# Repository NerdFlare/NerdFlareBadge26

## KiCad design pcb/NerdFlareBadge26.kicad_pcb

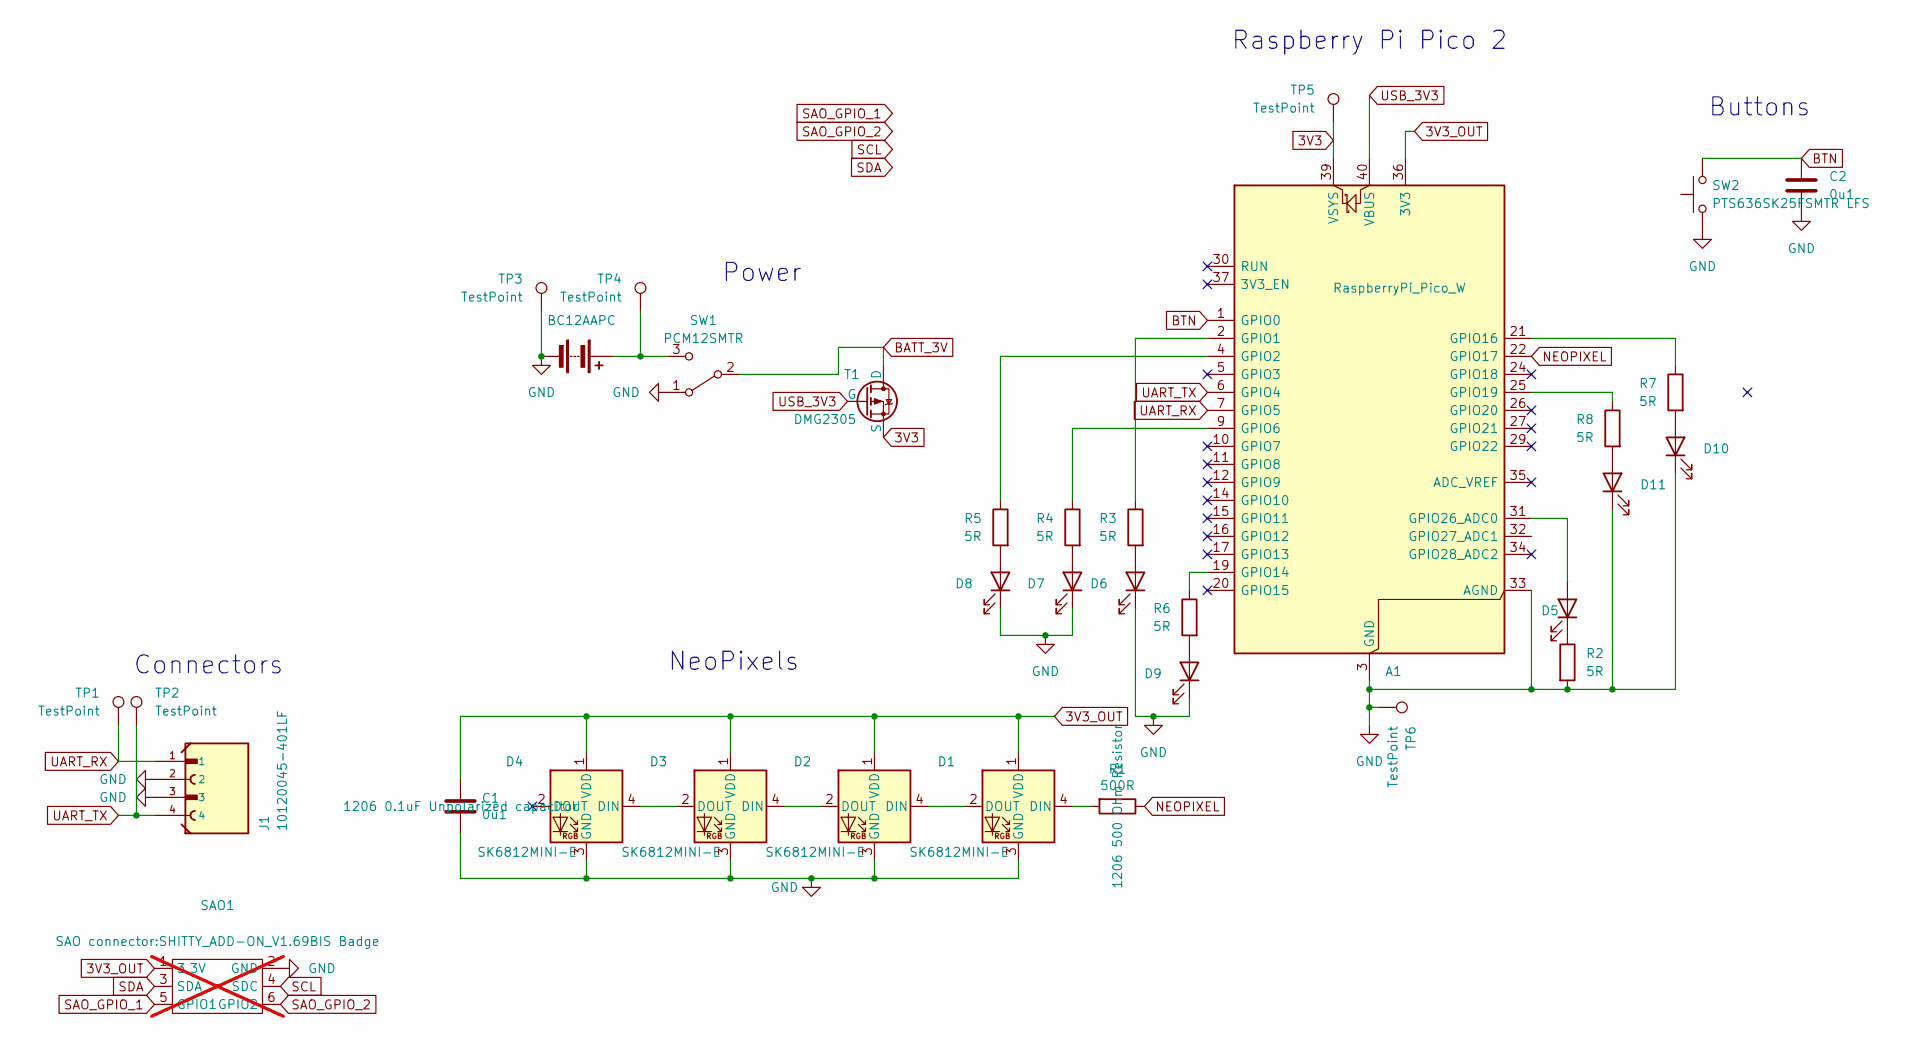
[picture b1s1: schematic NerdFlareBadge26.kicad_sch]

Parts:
A1: RaspberryPi_Pico_W; RPi_Pico_SMD
BT1: BC12AAPC; BAT_BC12AAPC
C1, C2: 0u1; C_1206_3216Metric_Pad1.33x1.80mm_HandSolder
D1, D2, D3, D4: SK6812MINI-E
D5, D6, D7, D8, D9, D10, D11: B1501TW--20P001013U1930; LED_1206_3216Metric_Pad1.42x1.75mm_HandSolder
J1: 10120045-401LF; AMPHENOL_10120045-401LF; PARTREV A
R1: 500R; R_1206_3216Metric_Pad1.30x1.75mm_HandSolder
R2, R3, R4, R5, R6, R7, R8: 5R; R_1206_3216Metric_Pad1.30x1.75mm_HandSolder
SAO1: SHITTY_ADD-ON_V1.69BIS Badge; not fitted
SW1: PCM12SMTR; SW_SPDT_PCM12
SW2: PTS636SK25FSMTR LFS; SMT Tactile Switch CK PTS636SK25FSMTR
T1: DMG2305; SOT-23
TP1, TP2, TP3, TP4, TP5, TP6: TestPoint; TestPoint_Pad_1.5x1.5mm

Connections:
3V3: A1.39 (VSYS), T1.2 (S), TP5.1
3V3_OUT: A1.36 (3V3), C1.1, D1.1 (VDD), D2.1 (VDD), D3.1 (VDD), D4.1 (VDD), SAO1.1 (3.3V)
BATT_3V: SW1.2 (B), T1.3 (D)
BTN: A1.1 (GPIO0), C2.1, SW2.2
GND: A1.3 (GND), A1.8 (GND), A1.13 (GND), A1.18 (GND), A1.23 (GND), A1.28 (GND), A1.33 (AGND), A1.38 (GND), BT1.2 (-), C1.2, C2.2, D1.3 (GND), D2.3 (GND), D3.3 (GND), D4.3 (GND), D6.1 (K), D7.1 (K), D8.1 (K), D9.1 (K), D10.1 (K), D11.1 (K), J1.2, J1.3, R2.2, SAO1.2 (GND), SW1.1 (A), SW2.1, TP3.1, TP6.1
NEOPIXEL: A1.22 (GPIO17), R1.1
unnamed: A1.2 (GPIO1), R3.1
unnamed: A1.4 (GPIO2), R5.1
unnamed: A1.9 (GPIO6), R4.1
unnamed: A1.19 (GPIO14), R6.1
unnamed: A1.21 (GPIO16), R7.1
unnamed: A1.25 (GPIO19), R8.1
unnamed: A1.31 (GPIO26_ADC0), D5.2 (A)
unnamed: BT1.1 (+), SW1.3 (C), TP4.1
unnamed: D1.4 (DIN), R1.2
unnamed: D1.2 (DOUT), D2.4 (DIN)
unnamed: D2.2 (DOUT), D3.4 (DIN)
unnamed: D3.2 (DOUT), D4.4 (DIN)
unnamed: D5.1 (K), R2.1
unnamed: D6.2 (A), R3.2
unnamed: D7.2 (A), R4.2
unnamed: D8.2 (A), R5.2
unnamed: D9.2 (A), R6.2
unnamed: D10.2 (A), R7.2
unnamed: D11.2 (A), R8.2
SAO_GPIO_1: SAO1.5 (GPIO1)
SAO_GPIO_2: SAO1.6 (GPIO2)
SCL: SAO1.4 (SDC)
SDA: SAO1.3 (SDA)
UART_RX: A1.7 (GPIO5), J1.1, TP1.1
UART_TX: A1.6 (GPIO4), J1.4, TP2.1
USB_3V3: A1.40 (VBUS), T1.1 (G)

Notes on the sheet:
Buttons
Power
NeoPixels
Connectors
Raspberry Pi Pico 2

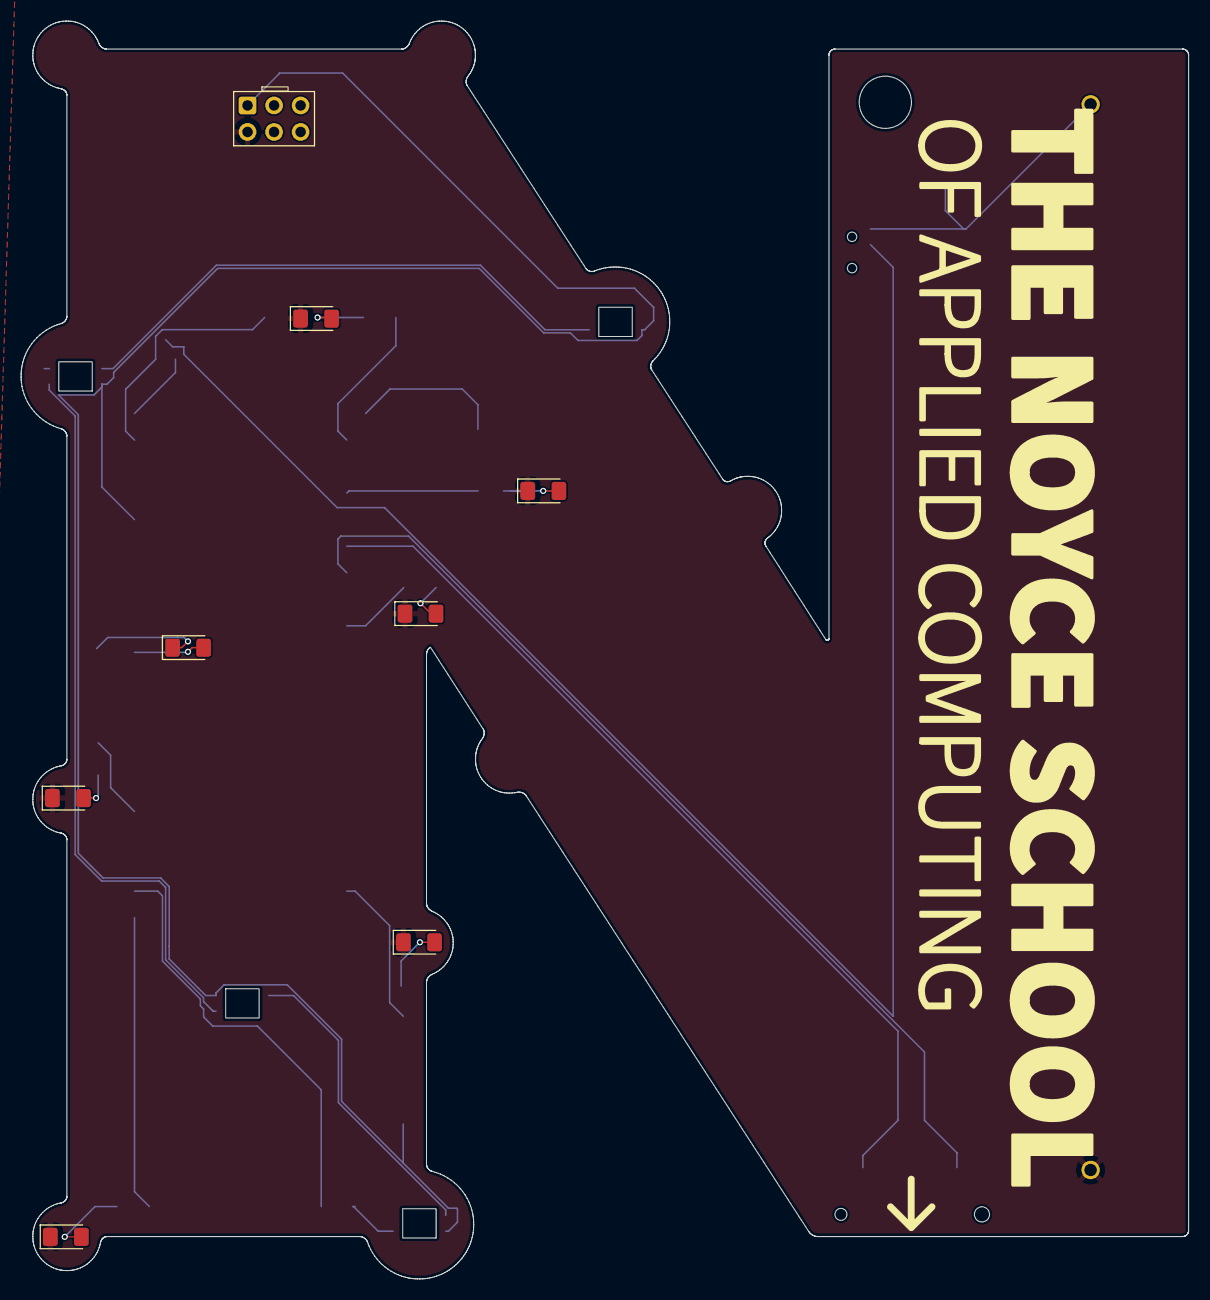
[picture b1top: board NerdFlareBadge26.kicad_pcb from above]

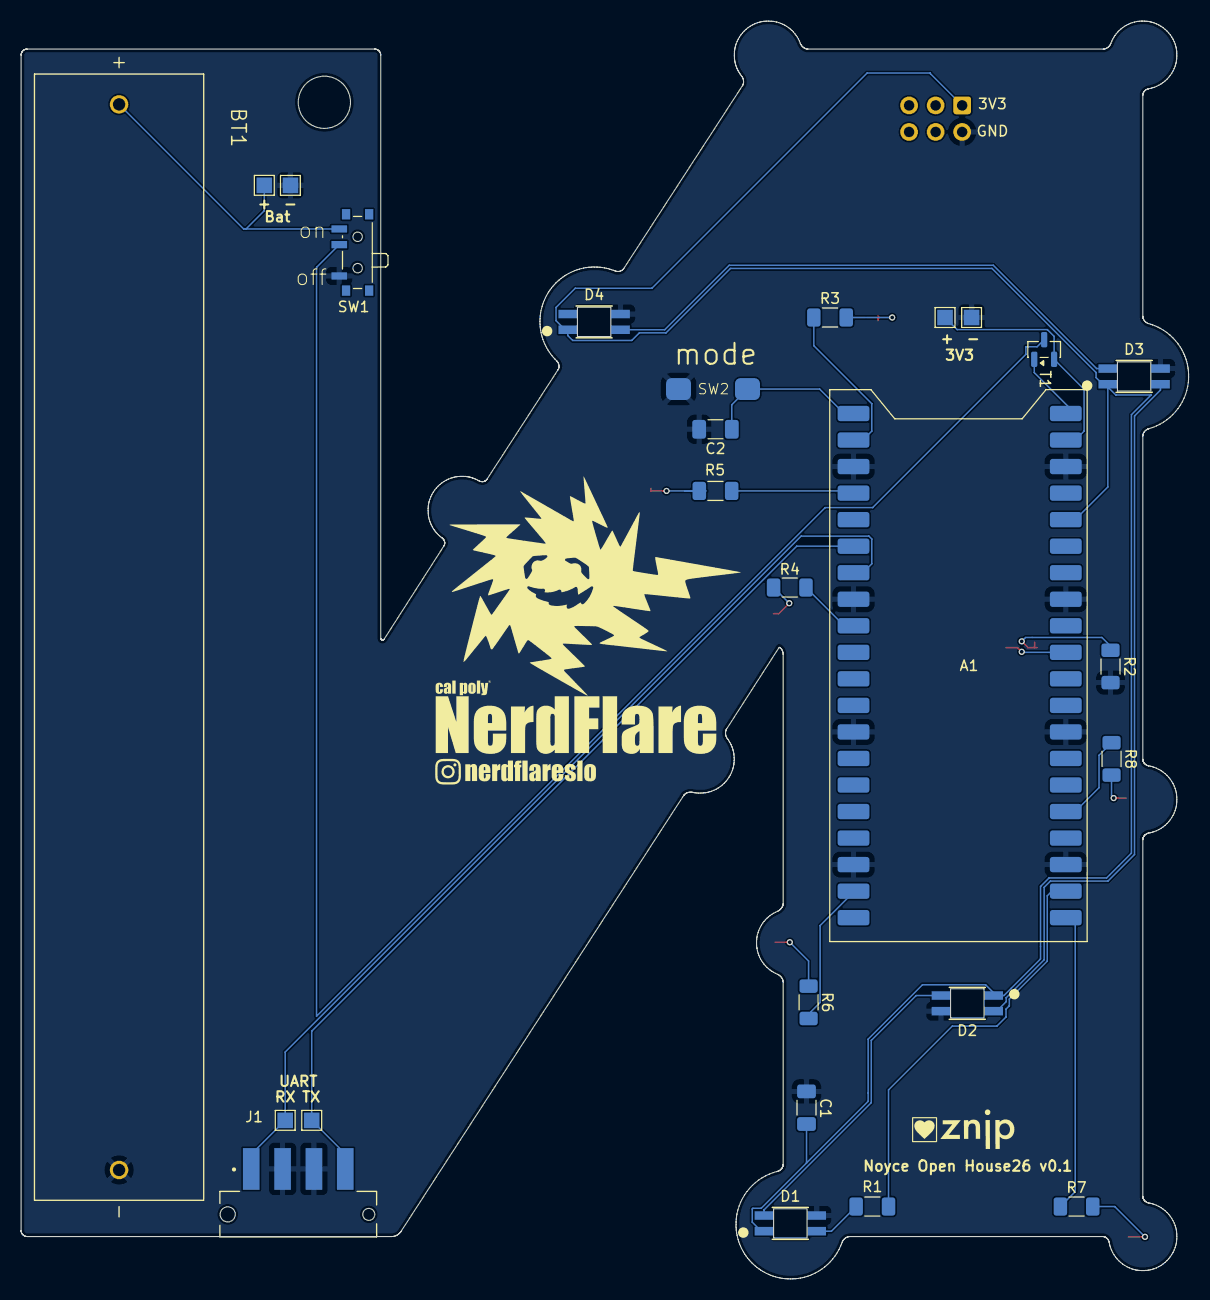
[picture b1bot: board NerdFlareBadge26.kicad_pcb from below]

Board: 2 copper layers, 111.7 x 120.4 mm, 34 parts (22 on the bottom side), 28 nets.

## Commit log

2026-03-31 Initial commit of v0.1 and sample code.
2026-04-03 v0 of firmware supporting game and sparkle mode. adding examples.py with a few unused LED animations, settings.json which keeps game and mode settings stateful, and requirements for necessary circuit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
2026-04-08 v0.1 of firmware. Updated GPIO ports to match v0.1 hardware, updated the anaimation logic a little bit, and tried to fix a race condition with changing the CURRENT_LEVEL in the uart task while acting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
2026-04-09 v0,1,1: Cleaned up the animation a bit when switching from game to sparkle mode; fixed a bug where the button was being checked before being fully pulled up; added LED brightness as a system setting;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
